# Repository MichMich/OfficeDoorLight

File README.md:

# Office Door Light

This repository includes the kicad files and firmware for my Office Door Light. 
More info about this project can be found here: https://michaelteeuw.nl/post/red-green-and-orange

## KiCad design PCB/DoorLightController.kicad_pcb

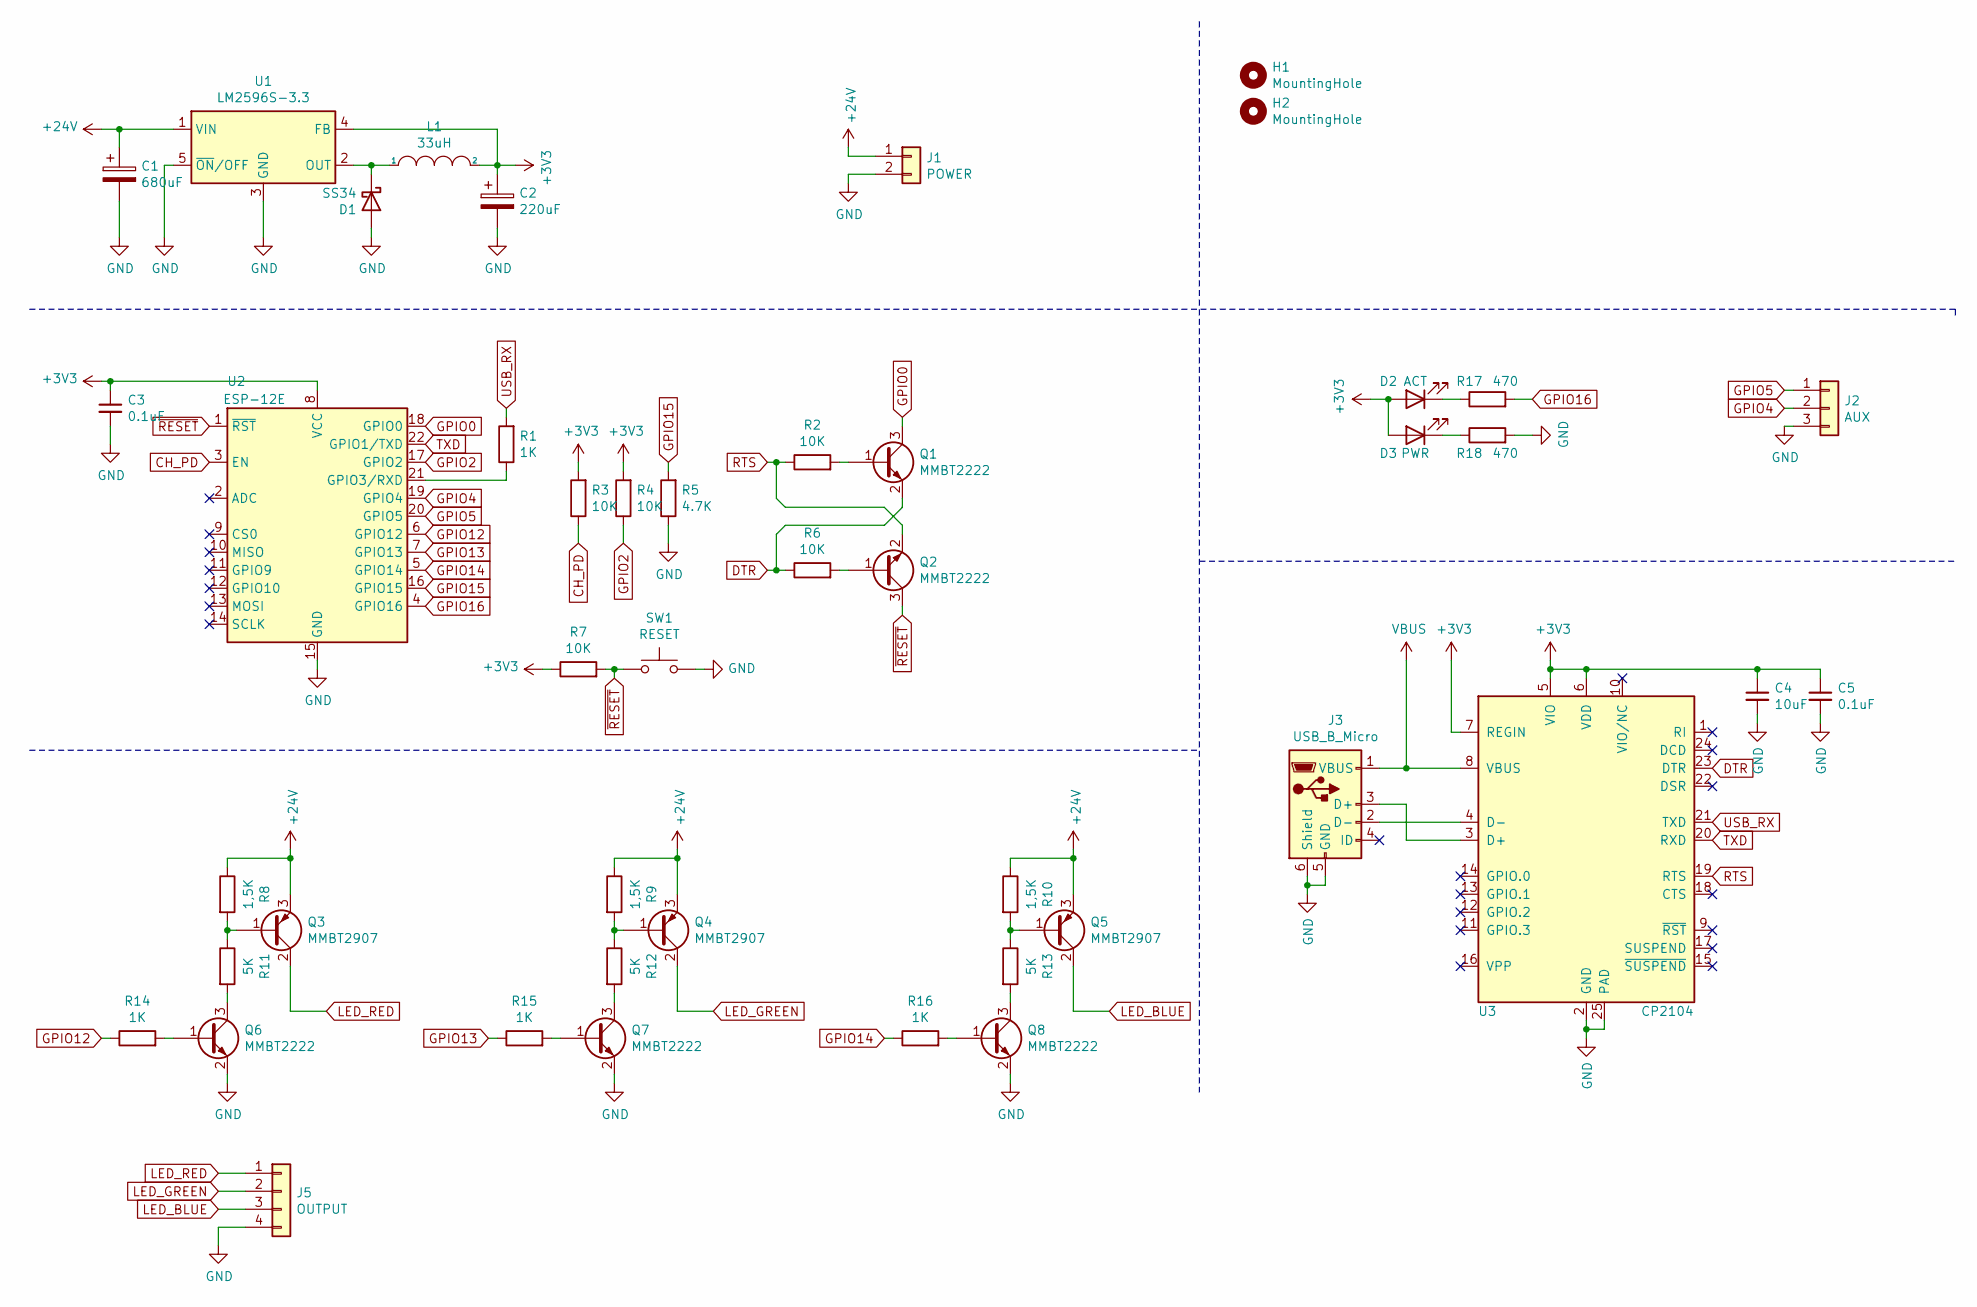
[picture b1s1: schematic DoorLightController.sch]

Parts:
C1: 680uF; CP_Radial_D10.0mm_P2.50mm
C2: 220uF; CP_Radial_D6.3mm_P2.50mm
C3, C5: 0.1uF; C_0805_2012Metric
C4: 10uF; C_0805_2012Metric
D1: SS34; D_SOD-123F
D2: ACT; LED_0805_2012Metric
D3: PWR; LED_0805_2012Metric
H1, H2: MountingHole; MountingHole_3.2mm_M3
J1: POWER; JST_XH_B2B-XH-A_1x02_P2.50mm_Vertical
J2: AUX; PinHeader_1x03_P2.54mm_Vertical
J3: USB_B_Micro; USB_Micro-B_Molex-105017-0001
J5: OUTPUT; JST_XH_B4B-XH-A_1x04_P2.50mm_Vertical
L1: 33uH; L_Pulse_PA4320
Q1, Q2, Q6, Q7, Q8: MMBT2222; SOT-23
Q3, Q4, Q5: MMBT2907; SOT-23
R1, R14, R15, R16: 1K; R_0805_2012Metric
R2, R3, R4, R6, R7: 10K; R_0805_2012Metric
R5: 4.7K; R_0805_2012Metric
R8, R9, R10: 1,5K; R_0805_2012Metric
R11, R12, R13: 5K; R_0805_2012Metric
R17, R18: 470; R_0805_2012Metric
SW1: RESET; SW_SPST_EVQPE1
U1: LM2596S-3.3; TO-263-5_TabPin3
U2: ESP-12E
U3: CP2104; QFN-24-1EP_4x4mm_P0.5mm_EP2.6x2.6mm

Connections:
+3V3: C2.1, C3.1, C4.1, C5.1, D2.2 (A), D3.2 (A), L1.2, R3.2, R4.2, R7.1, U1.4 (FB), U2.8 (VCC), U3.5 (VIO), U3.6 (VDD), U3.7 (REGIN)
+24V: C1.1, J1.1, Q3.3 (E), Q4.3 (E), Q5.3 (E), R8.1, R9.1, R10.1, U1.1 (VIN)
CH_PD: R3.1, U2.3 (EN)
DTR: Q1.2 (E), R6.1, U3.23 (DTR)
GND: C1.2, C2.2, C3.2, C4.2, C5.2, D1.2 (A), J1.2, J2.3, J3.5 (GND), J3.6 (Shield), J5.4, Q6.2 (E), Q7.2 (E), Q8.2 (E), R5.1, R18.2, SW1.2, U1.3 (GND), U1.5 (~ON~/OFF), U2.15 (GND), U3.2 (GND), U3.25 (PAD)
GPIO0: Q1.3 (C), U2.18 (GPIO0)
GPIO2: R4.1, U2.17 (GPIO2)
GPIO4: J2.2, U2.19 (GPIO4)
GPIO5: J2.1, U2.20 (GPIO5)
GPIO12: R14.1, U2.6 (GPIO12)
GPIO13: R15.1, U2.7 (GPIO13)
GPIO14: R16.1, U2.5 (GPIO14)
GPIO15: R5.2, U2.16 (GPIO15)
GPIO16: R17.2, U2.4 (GPIO16)
LED_BLUE: J5.3, Q5.2 (C)
LED_GREEN: J5.2, Q4.2 (C)
LED_RED: J5.1, Q3.2 (C)
unnamed: D1.1 (K), L1.1, U1.2 (OUT)
unnamed: D2.1 (K), R17.1
unnamed: D3.1 (K), R18.1
unnamed: J3.2 (D-), U3.4 (D-)
unnamed: J3.3 (D+), U3.3 (D+)
unnamed: Q1.1 (B), R2.2
unnamed: Q2.1 (B), R6.2
unnamed: Q3.1 (B), R8.2, R11.1
unnamed: Q4.1 (B), R9.2, R12.1
unnamed: Q5.1 (B), R10.2, R13.1
unnamed: Q6.1 (B), R14.2
unnamed: Q6.3 (C), R11.2
unnamed: Q7.1 (B), R15.2
unnamed: Q7.3 (C), R12.2
unnamed: Q8.1 (B), R16.2
unnamed: Q8.3 (C), R13.2
unnamed: R1.1, U2.21 (GPIO3/RXD)
RTS: Q2.2 (E), R2.1, U3.19 (RTS)
TXD: U2.22 (GPIO1/TXD), U3.20 (RXD)
USB_RX: R1.2, U3.21 (TXD)
VBUS: J3.1 (VBUS), U3.8 (VBUS)
~RESET: Q2.3 (C), R7.2, SW1.1, U2.1 (~RST)

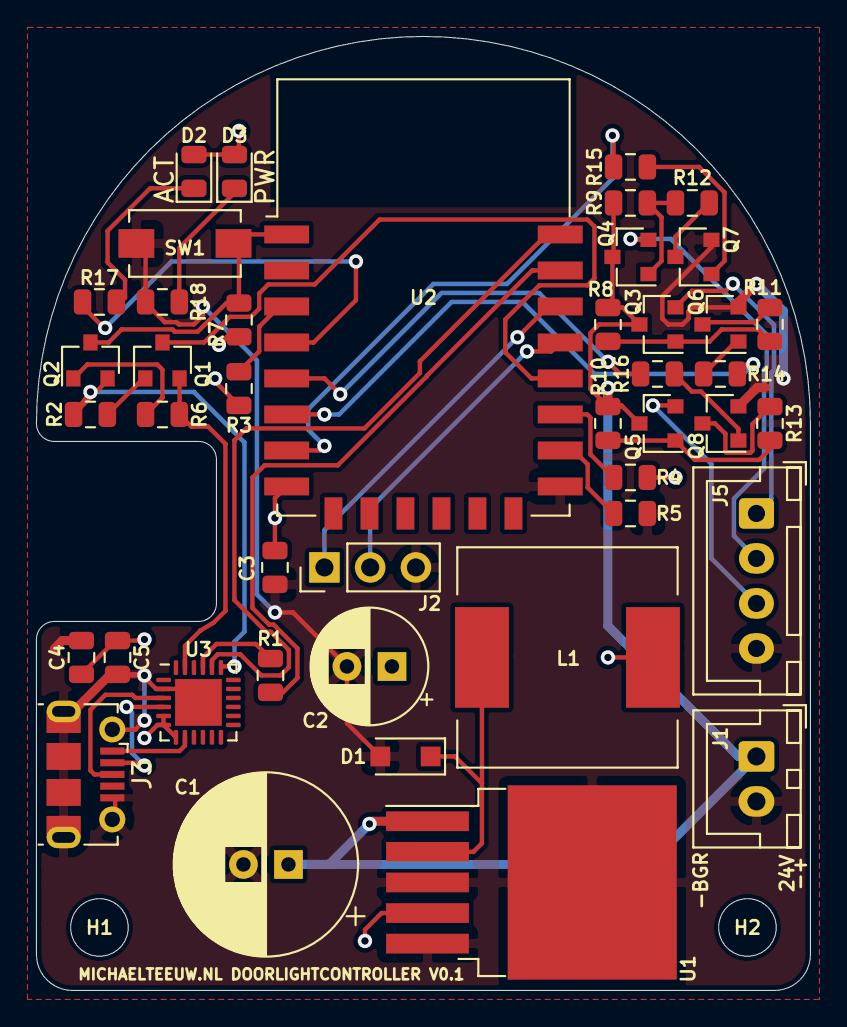
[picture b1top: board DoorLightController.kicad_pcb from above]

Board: 2 copper layers, 43.0 x 53.0 mm, 45 parts (0 on the bottom side), 39 nets.

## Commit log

2021-06-18 Cleanup file structure.
2021-06-19 Add Readme.
